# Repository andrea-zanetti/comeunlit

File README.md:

# Comelit SimpleBus blind bridge

Firmware and hardware for an Ethernet bridge to Comelit SimpleBus blind
modules (dual relay module 20004606), built on an ST NUCLEO-H563ZI with a
small interface shield.

The bridge is a **stateless actuator** with a signed HTTP API: a home
automation system asks it to read a blind, move it up/down/stop, or move a
group in sync, and can follow wall-switch presses live. The bridge owns the
bus timing and the module's rules (stop, reversal); it keeps no
configuration and no state.

> Not affiliated with or endorsed by Comelit. The protocol was
> reverse-engineered from bus captures for interoperability with equipment
> the author owns. Comelit and SimpleBus are trademarks of their owner.

## Why this might be useful to you

Even if you never control a blind, this repository gives you a working
starting point for SimpleBus, instead of a blank page:

* **A frame encoder and decoder** (`Core/Src/sb_frame.c`): preambles,
  UART-style bytes, checksums, and the 59-symbol shape modules use. Plain C,
  no hardware dependencies, covered by host tests.
* **A receiver and a transmitter with real timing:** edge capture to
  symbols (`Core/Src/simplebus_rx.c`), and hardware-timed transmission
  (`Core/Src/simplebus_tx.c`, `Core/Src/sb_tx_table.c`).
* **The hardware to get on the bus:** the interface shield
  (`hw/shield_rev1/`, KiCad 10, self-contained), with its known rev 1
  erratum documented.
* **Tools to explore the protocol:** a live stream of every frame on every
  bus and raw transmit (`tools/sbctl.py frames`, `tools/sbctl.py tx`), plus a
  generator for an HP 8175A test pattern (`tools/bench/`).
* **What is known about the protocol, and how it was found out:**
  [docs/simplebus_protocol_reference.md](docs/simplebus_protocol_reference.md)
  marks every statement by its source (scope, bridge or programmer) and
  lists the open questions.

## How it was made

The hardware was designed, built and debugged by the author. The firmware
was developed with the help of an AI assistant (Anthropic's Claude), under
the author's direction and review.

It is not untested generated code: the bus behaviour and timings described
here were checked on the bench with real test and measurement instruments (an Agilent MSO6034A
oscilloscope and an HP 8175A data generator) and on a real SimpleBus
installation, with real modules and wall switches. For example, the
module's 1.5 ms turnaround and the bit timings come from scope captures;
the extra pulse that made modules answer 33 ms late was found by comparing
two frame versions back to back on the live bus; and the hardware-timed
transmitter was checked by receiving 622 of 622 frames from the data
generator on one bus while the bridge transmitted on another.

## Status

| Part | State |
|------|-------|
| Bus receive / transmit, 3 buses | working on a live installation |
| Blind control (read, up, down, stop, reversal, batch) | working |
| Signed API, streams, raw admin access | working (firmware 0.1.0) |
| Shield | rev 1 built, **bus 1 unusable** (see below); rev 2 planned |

## Hardware

### Board

* **ST NUCLEO-H563ZI** (STM32H563ZI, Cortex-M33 at 250 MHz, Ethernet).
* **Power and clock come from the on-board ST-LINK**: the board is powered
  through the ST-LINK USB connector, and the MCU runs from the ST-LINK's
  8 MHz clock output (HSE bypass, PLL to 250 MHz). This is deliberate: do
  not "fix" it to HSI.
* In the installation, a PoE splitter provides both the Ethernet link and
  the 5 V USB supply; its cables are long enough to reach the Ethernet and
  ST-LINK USB ports on opposite sides of the board.
* Console: ST-LINK virtual COM port, 115200 8N1.

### Shield rev 1

One SimpleBus line per bus: an SN74LVC125A receiver into a TIM1 capture
input, and an SN74HCT125 driver with active-low output enable (10 kΩ
pull-ups keep the drivers tri-stated at boot). Bus *n* is on terminal
J(*n*+4).

| Bus | Terminal | RX (capture) | TX data | TX enable | State |
|-----|----------|--------------|---------|-----------|-------|
| 1 | J5 | PG12 (no capture) | — | — | **unusable** |
| 2 | J6 | PE9  TIM1_CH1 | PG14 | PC0 | working |
| 3 | J7 | PE11 TIM1_CH2 | PB6  | PC3 | working |
| 4 | J8 | PE14 TIM1_CH4 | PB7  | PB1 | working |

**Rev 1 erratum: bus 1 is fubar.** Its receiver is routed to D7 / PG12,
which has no timer capture channel, so the bridge cannot receive on it.
Rather than bodge the board, rev 1 runs on buses 2–4: three buses are
plenty for a typical flat (two in use here, one spare). Rev 2 will move
the bus 1 receiver to a capture-capable pin; its provisional map is
`hw/pins/shield_rev2.toml`.

The pin assignment is not hand-written anywhere in the code: it is
generated at build time from the TOML files in `hw/pins/` (board, connector
mating, shield revision) by `cmake/gen_pins.py`, which also checks that
every receiver lands on a TIM1 capture channel. The shield's KiCad files
live in `hw/shield_rev1/`.

## Security model

The bridge serves only `/api/v1/`, and **every request, response and stream
event is signed** with HMAC-SHA256 (hardware HASH unit) using a 32-byte key
compiled into the firmware. A per-boot random session (hardware RNG) and a
64-entry counter window reject replays. There is no TLS: the API gives
integrity and authenticity, not confidentiality. Put the bridge on a
network segment where only the home automation host can reach it.

Details: [docs/API.md](docs/API.md), section 3.

## Building

Requirements: `arm-none-eabi-gcc`, CMake ≥ 3.20, Python ≥ 3.11 (`tomllib`;
older Pythons need `pip install tomli`), and STM32CubeProgrammer's
`STM32_Programmer_CLI` for the `flash` target.

```sh
# 1. API key (never commit secrets.toml; it is gitignored)
printf '[auth]\nkey = "%s"\n' \
  "$(python3 -c 'import secrets; print(secrets.token_hex(32))')" > secrets.toml

# 2. Configure (shield rev 1 is the default) and build
cmake -B build -DSHIELD_REV=1
cmake --build build

# 3. Flash over the ST-LINK
cmake --build build --target flash
```

The build stops at configure time if `secrets.toml` is missing or its key is
malformed. The project is plain CMake and is **not** managed by STM32CubeMX:
there is no `.ioc`, and `main.c`, the HAL configuration and the FreeRTOS
configuration are ordinary source files.

**MAC address.** By default each board derives its Ethernet MAC from the
chip's 96-bit unique ID: a locally administered address (`x2:`, `x6:`, `xA:`
or `xE:` first octet), different on every board and stable across reflashes.
It is printed at boot (`[NET] MAC ...`). To pin a fixed one instead, for
example to keep an existing DHCP reservation:

```sh
cmake -B build -DSB_ETH_MAC=aa:bb:cc:dd:ee:ff
```

Configure fails if the value is malformed or a multicast address. Pass
`-DSB_ETH_MAC=` (empty) to go back to the derived address.

### First boot

On the console:

```
=== SimpleBus Bridge ===
[TX] shield rev 1, buses: 2(J6) 3(J7) 4(J8), LBT on
MAIN: starting kernel
[NET] MAC 02:1a:2b:3c:4d:5e (from chip UID)
[NET] Link up, starting DHCP...
[NET] DHCP address: 10.0.0.42
[CRYPTO] HASH HMAC-SHA256 + RNG OK (4 HMAC vectors, RNG); boot random ...
[API] session ...
[HTTP] Listening on port 80 (API v1 only)
```

The bridge uses DHCP and has no fallback address: if no lease arrives
within a minute it logs `[NET] No DHCP lease yet (still trying)`, keeps
trying, and answers as soon as it gets one. A reservation for the MAC above
gives it a stable address.

The `[CRYPTO]` line is the boot self-test of the HASH unit (RFC 4231 test
vectors) and the RNG. If it fails, the API refuses every request with
`503 crypto` and the console says which test failed.

## Using it

`tools/sbctl.py` is a signing command-line client (standard library only):

```sh
export SB_HOST=10.0.0.42
export SB_SECRETS=$PWD/secrets.toml

tools/sbctl.py health
tools/sbctl.py scan 2 1-32          # find modules on bus 2
tools/sbctl.py get 2:6
tools/sbctl.py up 2:6               # also: down, stop
tools/sbctl.py batch down 2:3 2:4 2:5
tools/sbctl.py events               # wall-switch presses and acks, live
tools/sbctl.py frames               # every frame on every bus
tools/sbctl.py tx 2 "21 06 00 00"   # raw frame (checksum appended)
```

The signing functions at the top of `sbctl.py` are a reference for writing
a client in any language.

## Repository layout

```
Core/            application (bus, blind logic, API, auth, streams), HAL config
LWIP/            network glue and the HTTP server
Drivers/         ST HAL v1.6.0, CMSIS, BSP (vendored)
Middlewares/     FreeRTOS, lwIP (vendored)
hw/pins/         pin maps (TOML) -> generated board_pins.h
hw/shield_rev1/  shield KiCad files
cmake/           toolchain file, pin-map and secret generators
tools/sbctl.py   signed CLI client
tools/bench/     bench helpers (HP 8175A test pattern generator)
tests/host/      host tests and the end-to-end fake bridge
docs/            API and protocol reference
```

## Tests

The bus-independent parts (frame codec, receiver, blind logic, API,
authentication, streams, MAC derivation, the transmitter's DMA table) build and run on a PC; OpenSSL stands in for the
HASH unit and a simulated bus for the modules.

```sh
make -C tests/host        # C tests
make -C tests/host e2e    # sbctl.py against the firmware's API on a socket
```

## Documentation

* [docs/API.md](docs/API.md): the HTTP API, signing, endpoints, errors.
* [docs/simplebus_protocol_reference.md](docs/simplebus_protocol_reference.md):
  the bus protocol as reverse-engineered, with the annotated scope capture.

## Known limitations

* Shield rev 1: bus 1 unusable (above).
* Modules do not announce the end of travel; a client that needs to know a
  blind has stopped must poll it.
* No automatic retries: a press is not idempotent, so a missing ack is
  reported and the client decides.
* Open protocol questions are listed at the end of the protocol reference.

## Licence

This project's own code and its documentation and hardware use different
licences, and the vendored or ST-derived code keeps its own. In short: any
use except commercial use. This is a summary, not legal advice; the licence
texts decide.

| What | Licence |
|------|---------|
| Firmware written for this project, `cmake/`, `tools/`, `tests/` | [PolyForm Noncommercial 1.0.0](LICENSE) |
| `docs/`, `hw/` (except `hw/shield_rev1/lib/`) | [CC BY-NC-SA 4.0](LICENSE-docs-hw) |
| `hw/shield_rev1/lib/` (symbols, footprints, 3D models from SnapEDA and KiCad) | CC BY-SA 4.0, see [its NOTICE](hw/shield_rev1/lib/NOTICE.md) |
| The zmonad name and logo (the `LOGO` footprint on the board) | Not licensed: all rights reserved |
| Files with an STMicroelectronics copyright header (in `Core/` and `LWIP/`) | ST's terms, see below |
| `Drivers/STM32H5xx_HAL_Driver`, `Drivers/BSP` | BSD 3-Clause (STMicroelectronics) |
| `Drivers/CMSIS` | Apache 2.0 (Arm, STMicroelectronics) |
| `Middlewares/Third_Party/FreeRTOS` | MIT (Amazon) |
| `Middlewares/Third_Party/LwIP` | BSD 3-Clause (Swedish Institute of Computer Science) |

**ST-derived files.** Some files in `Core/` and `LWIP/` were generated by
STM32CubeMX or adapted from STM32CubeH5; they keep their STMicroelectronics
header and stay under ST's terms, including the changes made here. The
network glue (`LWIP/Target/ethernetif.[ch]`, `LWIP/App/app_ethernet.[ch]`)
comes from ST's `LwIP_HTTP_Server_Socket_RTOS` application; STM32CubeH5
licenses its application projects under ST's SLA0044, which allows
redistribution in source form if the notice is kept, requires the code to
run only on ST devices, and does not allow placing it under open-source
terms. None of this limits running the bridge on its intended STM32H563.

**zmonad logo.** The board carries the author's zmonad logo. It is not
covered by any licence here: unmodified copies of the repository may keep
it, but modified or derived boards must remove the `LOGO` footprint.

PolyForm Noncommercial is not an open-source licence in the OSI sense: it
allows personal, hobby, research, educational and other noncommercial use,
and does not allow commercial use without separate permission.

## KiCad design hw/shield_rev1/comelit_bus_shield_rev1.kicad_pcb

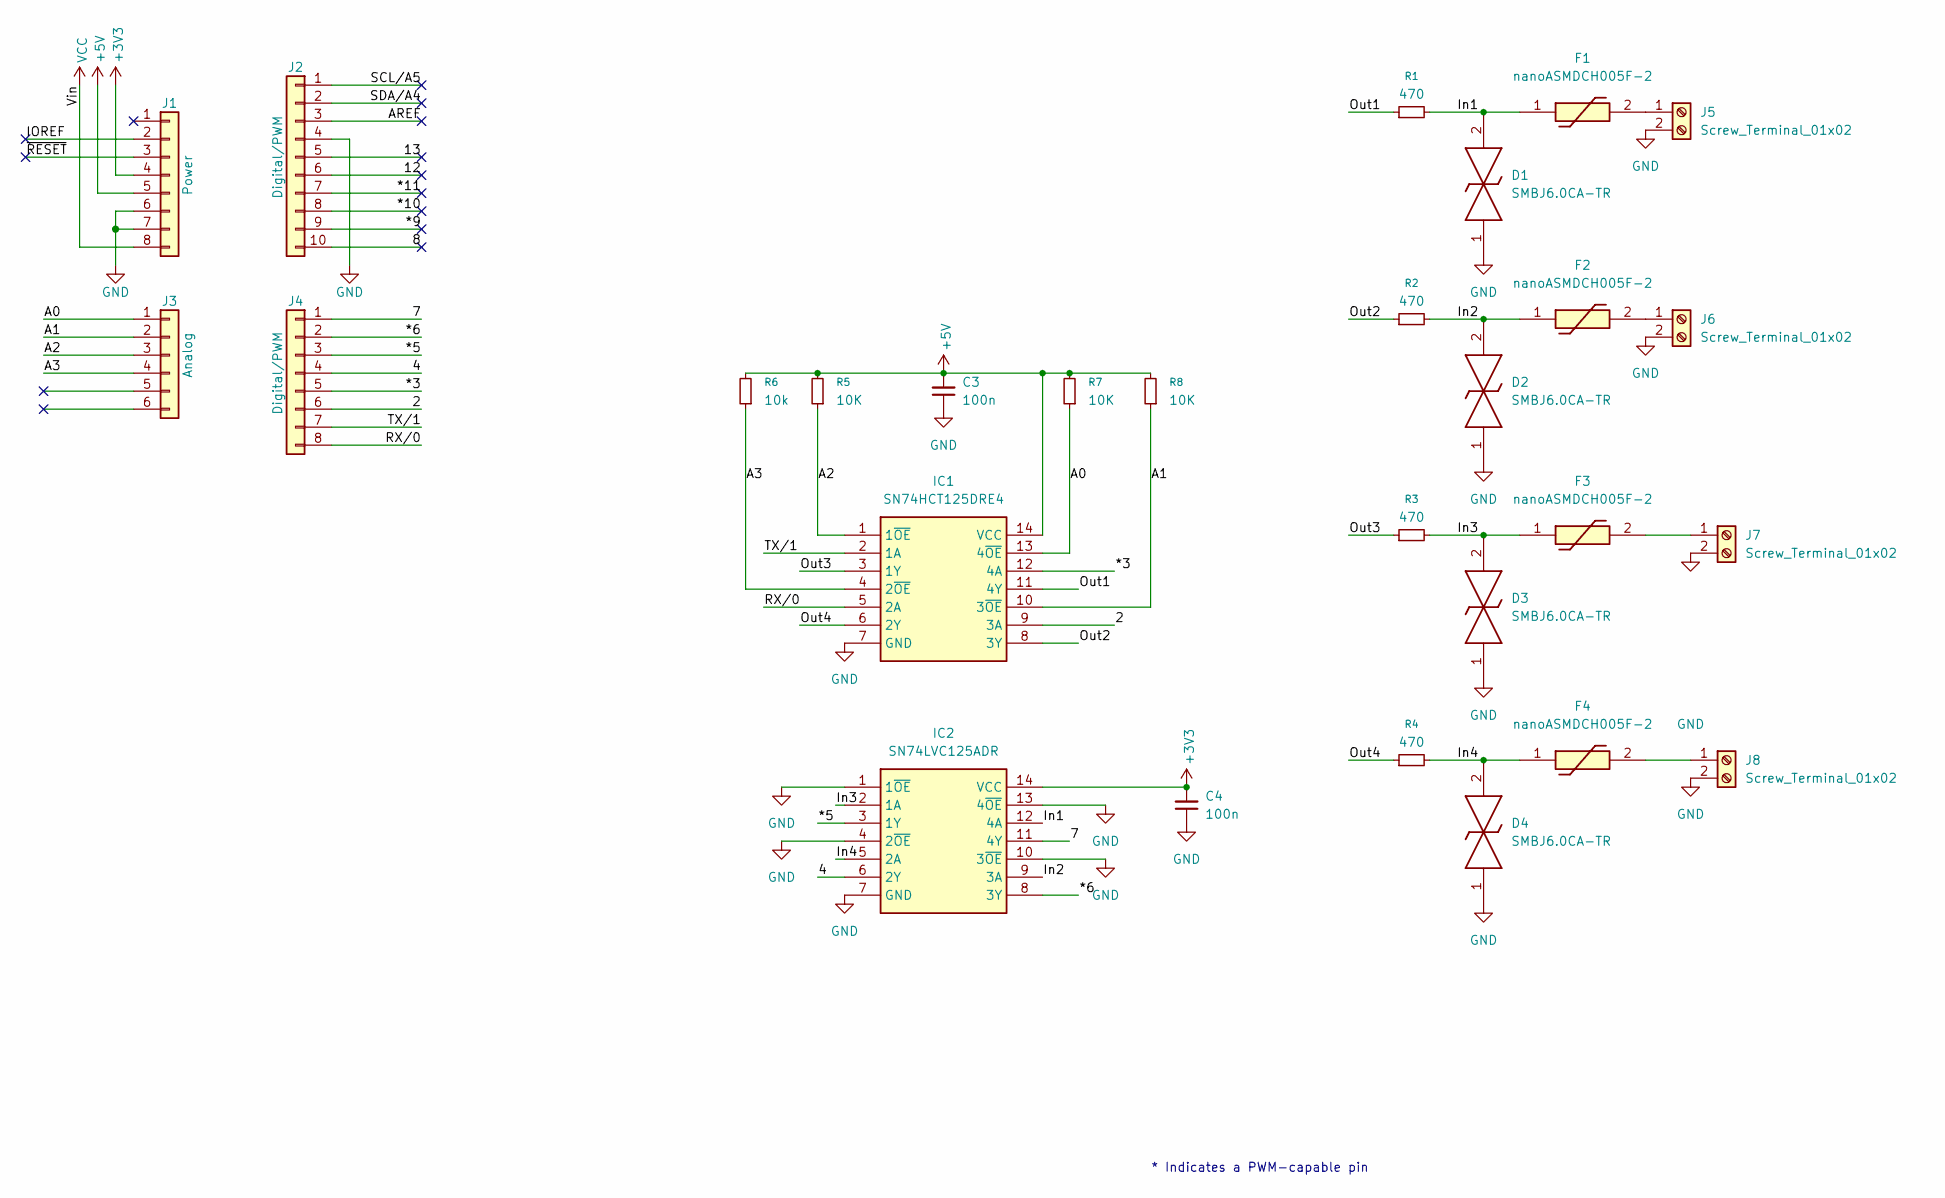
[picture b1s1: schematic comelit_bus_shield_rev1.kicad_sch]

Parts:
C3, C4: 100n; C_0603_1608Metric_Pad1.08x0.95mm_HandSolder
D1, D2, D3, D4: SMBJ6.0CA-TR; DIONM5436X265N; Mouser Part Number 511-SMBJ6.0CA-TR
F1, F2, F3, F4: nanoASMDCH005F-2; FUSC3216X85N; Mouser Part Number 576-NANOASMDCH005F-2
IC1: SN74HCT125DRE4; SOIC127P600X175-14N; Mouser Part Number 595-SN74HCT125DRE4
IC2: SN74LVC125ADR; SOIC127P600X175-14N; Mouser Part Number 595-SN74LVC125ANSR
J1: Power; PinSocket_1x08_P2.54mm_Vertical
J2: Digital/PWM; PinSocket_1x10_P2.54mm_Vertical
J3: Analog; PinSocket_1x06_P2.54mm_Vertical
J4: Digital/PWM; PinSocket_1x08_P2.54mm_Vertical
J5, J6, J7, J8: Screw_Terminal_01x02; TerminalBlock_Phoenix_MKDS-1-2-3.81_1x02_P3.81mm_Horizontal
R1, R2, R3, R4: 470; R_0603_1608Metric_Pad0.98x0.95mm_HandSolder
R5, R7, R8: 10K; R_0603_1608Metric_Pad0.98x0.95mm_HandSolder
R6: 10k; R_0603_1608Metric_Pad0.98x0.95mm_HandSolder

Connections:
+3V3: C4.2, IC2.14 (VCC), J1.4
+5V: C3.2, IC1.14 (VCC), J1.5, R5.2, R6.2, R7.2, R8.2
/2: IC1.9 (3A), J4.6
/4: IC2.6 (2Y), J4.4
/7: IC2.11 (4Y), J4.1
/8: J2.10
/12: J2.6
/13: J2.5
/*3: IC1.12 (4A), J4.5
/*5: IC2.3 (1Y), J4.3
/*6: IC2.8 (3Y), J4.2
/*9: J2.9
/*10: J2.8
/*11: J2.7
/A0: IC1.13 (4~OE), J3.1, R7.1
/A1: IC1.10 (3~OE), J3.2, R8.1
/A2: IC1.1 (1~OE), J3.3, R5.1
/A3: IC1.4 (2~OE), J3.4, R6.1
/AREF: J2.3
/IOREF: J1.2
/In1: D1.2, F1.1, IC2.12 (4A), R1.2
/In2: D2.2, F2.1, IC2.9 (3A), R2.2
/In3: D3.2, F3.1, IC2.2 (1A), R3.2
/In4: D4.2, F4.1, IC2.5 (2A), R4.2
/Out1: IC1.11 (4Y), R1.1
/Out2: IC1.8 (3Y), R2.1
/Out3: IC1.3 (1Y), R3.1
/Out4: IC1.6 (2Y), R4.1
/RX/0: IC1.5 (2A), J4.8
/SCL/A5: J2.1
/SDA/A4: J2.2
/TX/1: IC1.2 (1A), J4.7
/~RESET: J1.3
GND: C3.1, C4.1, D1.1, D2.1, D3.1, D4.1, IC1.7 (GND), IC2.1 (1~OE), IC2.4 (2~OE), IC2.7 (GND), IC2.10 (3~OE), IC2.13 (4~OE), J1.6, J1.7, J2.4, J5.2, J6.2, J7.2, J8.2
unnamed: F1.2, J5.1
unnamed: F2.2, J6.1
unnamed: F3.2, J7.1
unnamed: F4.2, J8.1
VCC: J1.8

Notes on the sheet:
* Indicates a PWM-capable pin

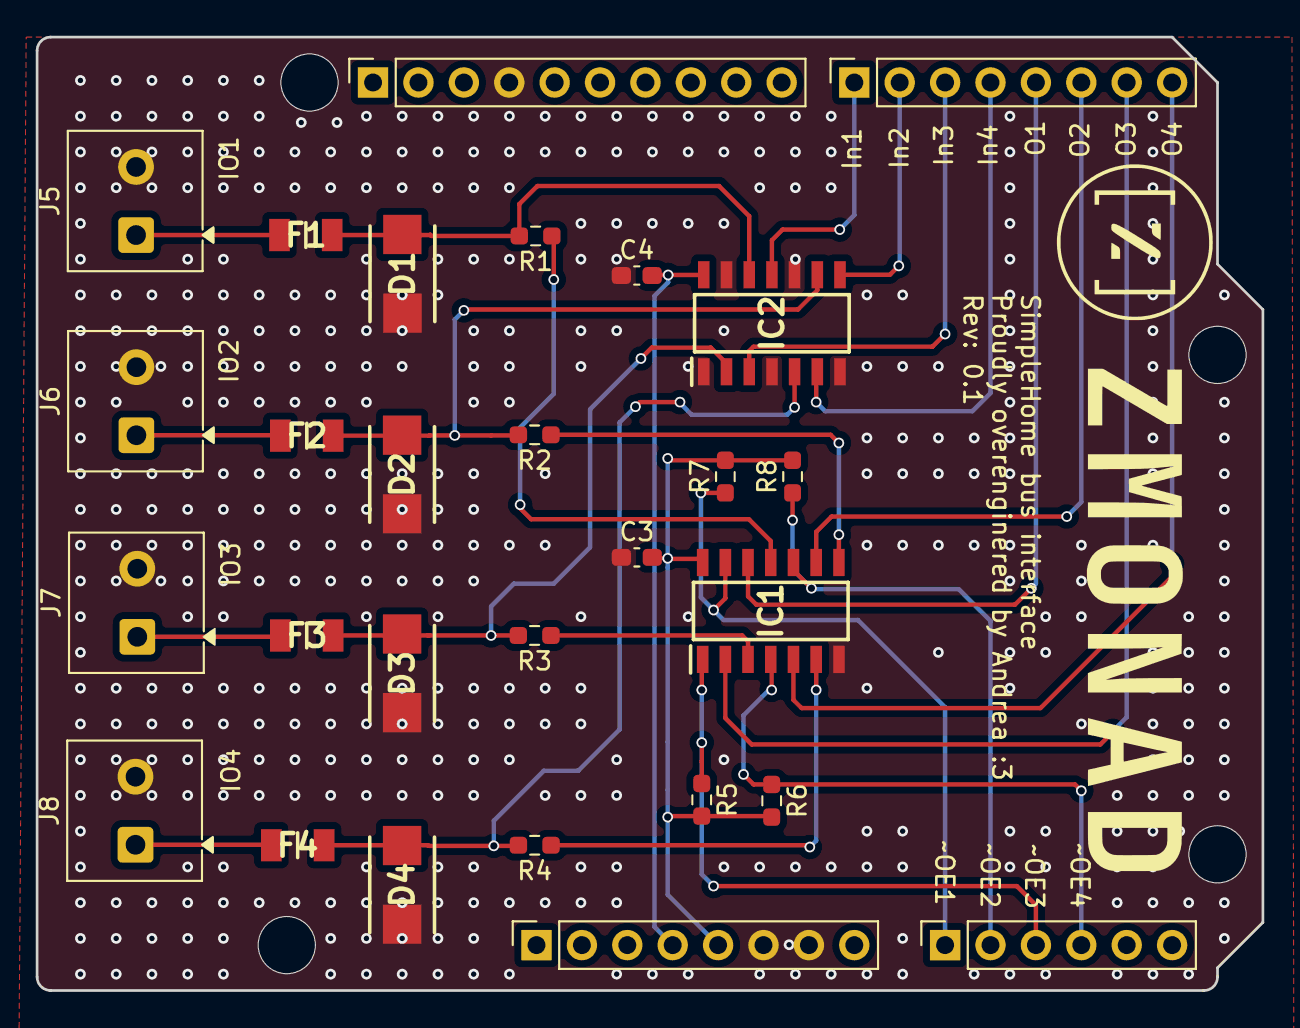
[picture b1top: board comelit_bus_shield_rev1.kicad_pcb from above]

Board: 2 copper layers, 68.6 x 53.3 mm, 33 parts (0 on the bottom side), 27 nets.

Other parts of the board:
MH1, MH2, MH3, MH4: MountingHole_3.2mm
logo: LOGO
